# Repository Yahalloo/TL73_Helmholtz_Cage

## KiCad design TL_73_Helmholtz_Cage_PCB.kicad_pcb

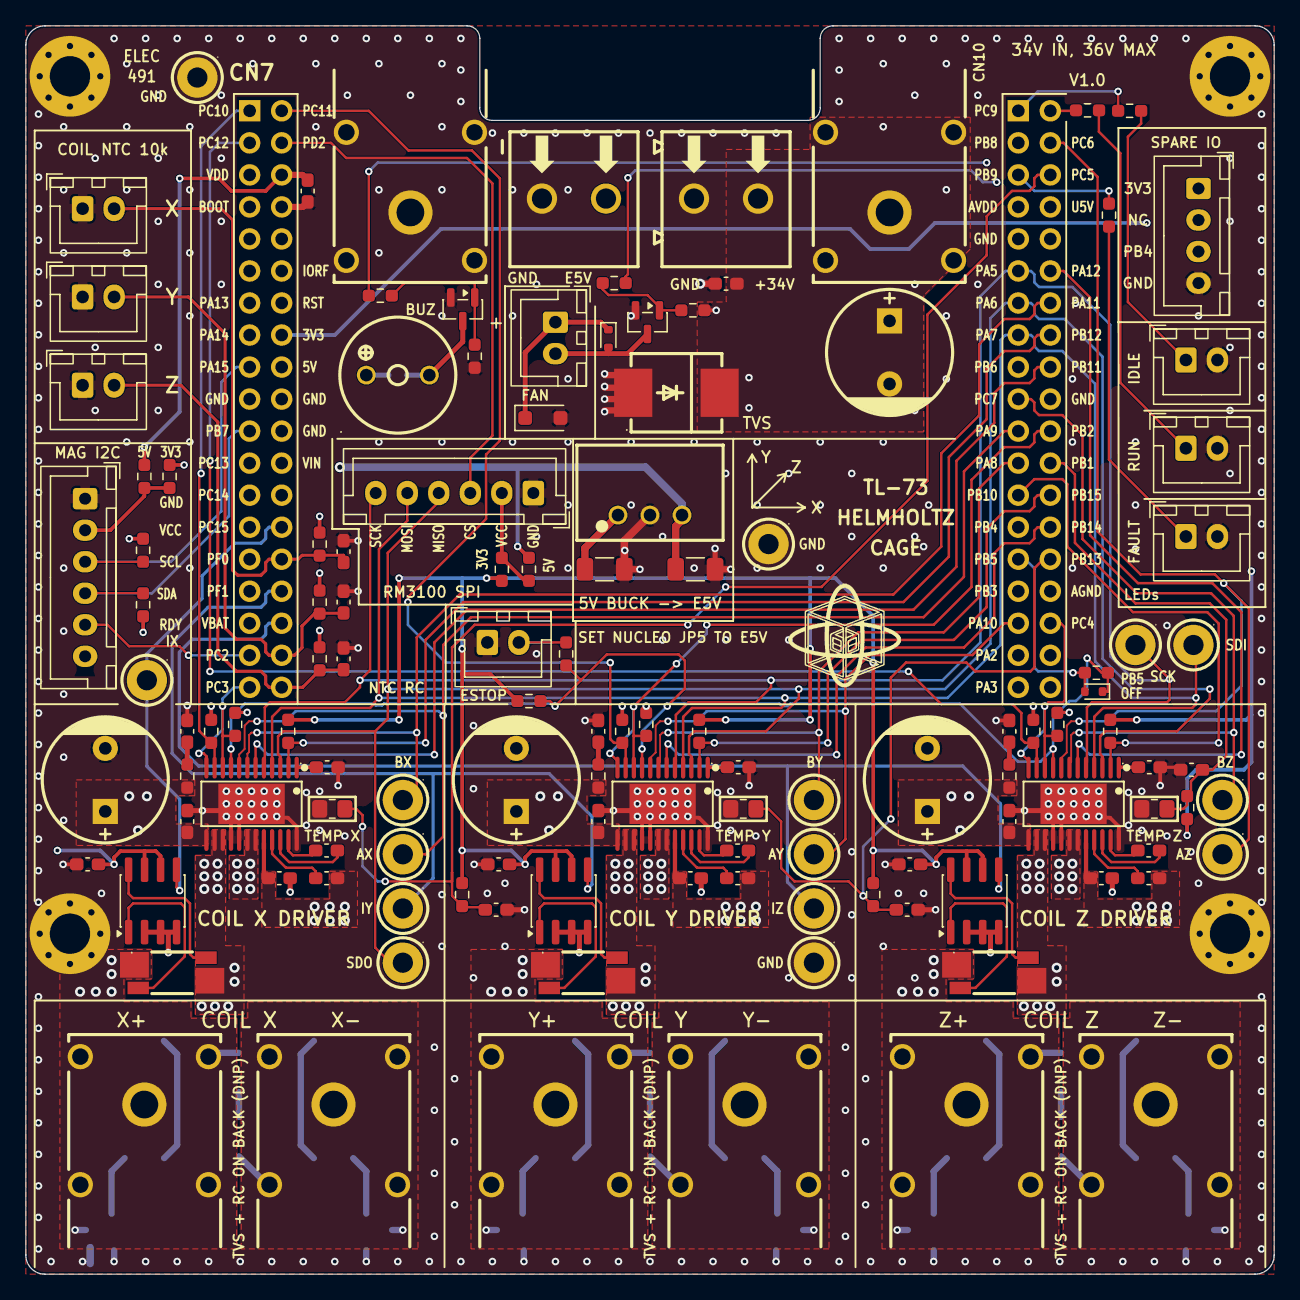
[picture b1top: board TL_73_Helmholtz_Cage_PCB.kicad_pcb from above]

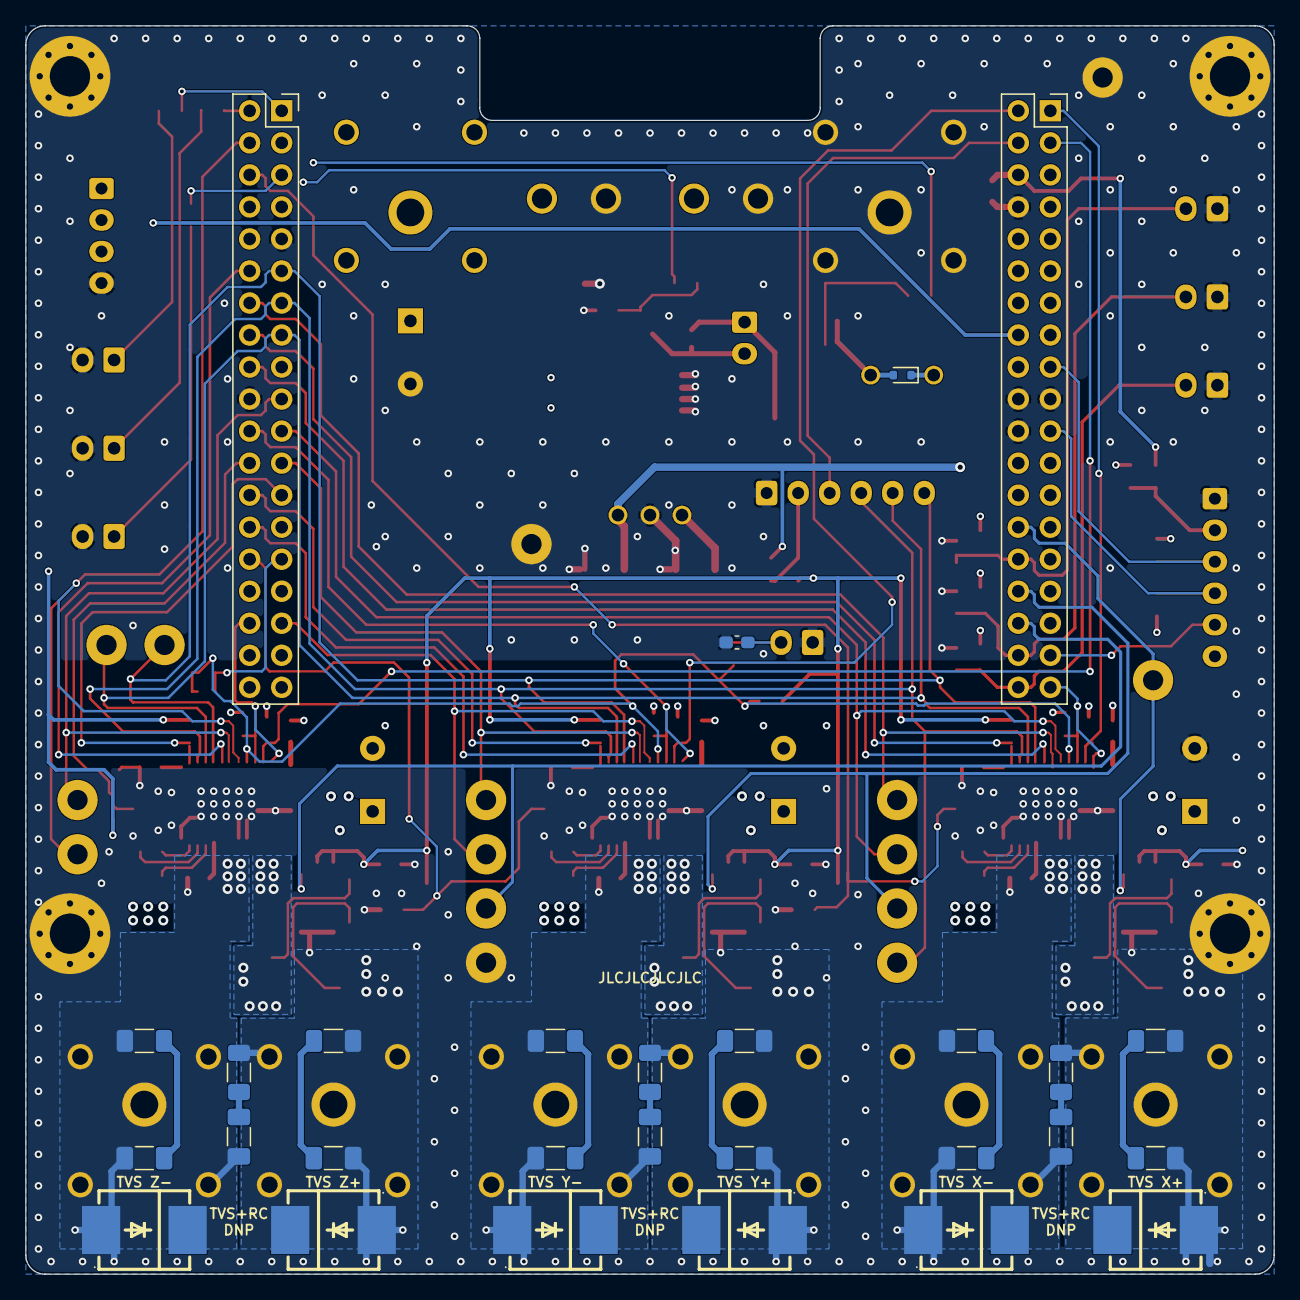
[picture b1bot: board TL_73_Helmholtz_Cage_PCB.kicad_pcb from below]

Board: 4 copper layers, 99.0 x 99.0 mm, 157 parts (28 on the bottom side), 95 nets.

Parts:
BZ201: TMB09A05; BUZ-TH_BD9.0-P5.00-D0.6-L-FD
C101: 10uF; C_1206_3216Metric_Pad1.33x1.80mm_HandSolder
C102: 22uF; C_1206_3216Metric_Pad1.33x1.80mm_HandSolder
C201, C202, C302, C305, C402, C405, C502, C505, C601, C701, C801, C901, C1001, C1101, C1202, C1401, C1402, C1403: 100nF; C_0603_1608Metric_Pad1.08x0.95mm_HandSolder
C301, C304, C401, C404, C501, C504: 1uF; C_0603_1608Metric_Pad1.08x0.95mm_HandSolder
C303, C403, C503: 47nF; C_0603_1608Metric_Pad1.08x0.95mm_HandSolder
C306, C406, C506: 10nF; C_0603_1608Metric_Pad1.08x0.95mm_HandSolder
C307, C407, C507: 330uF; CAP-TH_D10.0-P5.00_PA50V330M10X15_TL73
C1201: 470uF; CAP-TH_D10.0-P5.00_50ZLJ470M10X20_TL73
C1203, C1204, C1205, C1206, C1207, C1208, C1209, C1210, C1211: 470pF; C_1206_3216Metric_Pad1.33x1.80mm_HandSolder
CN1201, CN1203, CN1205, CN1207: 24.245.1; CONN-TH_24.245.1_RED_TL73
CN1202, CN1204, CN1206, CN1208: 24.245.2; CONN-TH_24.245.2_BLACK_TL73
D201: SMF5.0A; D_SOD-123F
D202, D203, D204: RB521S30T1G; D_SOD-523
D1201, D1202, D1203, D1204, D1205, D1206, D1207: SMDJ36A; SMC_L7.1-W6.2-LS8.1-RD
H101, H102, H103, H104: MountingHole_Pad; MountingHole_3.2mm_M3_Pad_Via
J201: CN7; PinSocket_2x19_P2.54mm_Vertical
J202: CN10; PinSocket_2x19_P2.54mm_Vertical
J203: LED_IDLE; JST_XH_B2B-XH-A_1x02_P2.50mm_Vertical
J204: STOP_SW_JST_XH; JST_XH_B2B-XH-A_1x02_P2.50mm_Vertical
J205: SPARE_IO_JST_XH; JST_XH_B4B-XH-A_1x04_P2.50mm_Vertical
J206: FAN_JST_XH; JST_XH_B2B-XH-A_1x02_P2.50mm_Vertical
J207: LED_RUN; JST_XH_B2B-XH-A_1x02_P2.50mm_Vertical
J208: LED_FAULT; JST_XH_B2B-XH-A_1x02_P2.50mm_Vertical
J901, J1001, J1101: NTC_JST_XH; JST_XH_B2B-XH-A_1x02_P2.50mm_Vertical
J1301: RM3100_JST_XH; JST_XH_B6B-XH-A_1x06_P2.50mm_Vertical
J1302: RM3100_SPI; JST_XH_B6B-XH-A_1x06_P2.50mm_Vertical
Q204, Q205: AO3400A; SOT-23
R104, R214, R215: 100k; R_0603_1608Metric_Pad0.98x0.95mm_HandSolder
R201, R202, R203: 150Ω; R_0603_1608Metric_Pad0.98x0.95mm_HandSolder
R204, R301, R302, R401, R402, R501, R502, R901, R1001, R1101, R1401, R1402, R1403: 10k; R_0603_1608Metric_Pad0.98x0.95mm_HandSolder
R205, R303, R403, R503: 330Ω; R_0603_1608Metric_Pad0.98x0.95mm_HandSolder
R209, R210: 100Ω; R_0603_1608Metric_Pad0.98x0.95mm_HandSolder
R304, R404, R504: 3.3Ω; R_0603_1608Metric_Pad0.98x0.95mm_HandSolder
R601, R701, R801: 10mΩ; RES-SMD_L6.4-W3.2_WSK2512R0100FEA
R1201, R1202, R1203, R1204, R1205, R1206, R1207, R1208, R1209: 33R; R_1206_3216Metric_Pad1.30x1.75mm_HandSolder
R1301, R1302: 2.2k; R_0603_1608Metric_Pad0.98x0.95mm_HandSolder
R1303, R1304, R1305, R1306: 0R; R_0603_1608Metric_Pad0.98x0.95mm_HandSolder
TH1401, TH1402, TH1403: 10k NTC; R_0805_2012Metric_Pad1.20x1.40mm_HandSolder
TP1, TP2, TP3, TP4, TP5, TP6, TP7, TP8, TP9, TP10, TP11, TP12, TP13, TP14, TP15: 5005; TESTPOINT-TH_BD3.2-D1.6_RED_TL73
U101: K7805-1000R3_C2992391; PWRM-TH_YLPTEC_K78XX-1000R3
U301, U401, U501: DRV8873SPWPR; HTSSOP-24_L7.8-W4.4-P0.65-LS6.4-TL-EP
U601, U701, U801: INA240A1DR; SOIC-8_3.9x4.9mm_P1.27mm
U1202: KF128-5.08-2P; CONN-TH_P5.08_KF128-5.08-2P
U1204: KF128-5.08-2P; CONN-TH_P5.08_KF128-5.08-2P_TL73_b

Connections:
+3V3: C601.1, C701.1, C801.1, J201.16, J205.1, R204.1, R301.1, R401.1, R501.1, R901.2, R1001.2, R1101.2, R1301.2, R1302.2, R1303.2, R1305.2, R1401.2, R1402.2, R1403.2, U601.6 (V+), U601.7 (REF1), U701.6 (V+), U701.7 (REF1), U801.6 (V+), U801.7 (REF1)
+34V: C101.1, C302.1, C304.1, C305.1, C307.1, C402.1, C404.1, C405.1, C407.1, C502.1, C504.1, C505.1, C507.1, C1201.1, C1202.1, CN1201.1, CN1201.2, D1201.1, R304.1, R404.1, R504.1, U101.1 (VIN), U301.13 (13VM), U301.20 (20VM), U401.13 (13VM), U401.20 (20VM), U501.13 (13VM), U501.20 (20VM), U1202.1
/BUZZER: J202.31, R210.1
/CurrentSense_CoilX/Icoil1: R601.4 (I1), U301.14 (14OUT2), U301.15 (15OUT2)
/CurrentSense_CoilX/Icoil2: CN1203.1, CN1203.2, D1202.1, R601.1 (I2), R1201.1, R1204.1
/CurrentSense_CoilX/SENSE_N: R601.2 (E2), U601.1 (-)
/CurrentSense_CoilX/SENSE_P: R601.3 (E1), U601.8 (+)
/CurrentSense_CoilY/Icoil1: R701.4 (I1), U401.14 (14OUT2), U401.15 (15OUT2)
/CurrentSense_CoilY/Icoil2: CN1205.1, CN1205.2, D1204.1, R701.1 (I2), R1202.1, R1206.1
/CurrentSense_CoilY/SENSE_N: R701.2 (E2), U701.1 (-)
/CurrentSense_CoilY/SENSE_P: R701.3 (E1), U701.8 (+)
/CurrentSense_CoilZ/Icoil1: R801.4 (I1), U501.14 (14OUT2), U501.15 (15OUT2)
/CurrentSense_CoilZ/Icoil2: CN1207.1, CN1207.2, D1206.1, R801.1 (I2), R1203.1, R1208.1
/CurrentSense_CoilZ/SENSE_N: R801.2 (E2), U801.1 (-)
/CurrentSense_CoilZ/SENSE_P: R801.3 (E1), U801.8 (+)
/DRV_DISABLE: D202.1, R104.1, R204.2, R205.1, U301.9 (9DISABLE), U401.9 (9DISABLE), U501.9 (9DISABLE)
/DRV_OFF: D202.2, J202.29, R104.2
/External_Connectors/CoilX-: C1203.2, CN1204.1, CN1204.2, D1203.1, R1205.2, U301.18 (18OUT1), U301.19 (19OUT1)
/External_Connectors/CoilY-: C1204.2, CN1206.1, CN1206.2, D1205.1, R1207.2, U401.18 (18OUT1), U401.19 (19OUT1)
/External_Connectors/CoilZ-: C1205.2, CN1208.1, CN1208.2, D1207.1, R1209.2, U501.18 (18OUT1), U501.19 (19OUT1)
/FAN_EN: J202.17, R209.1
/IPROPI_X: J201.37, R303.1, U301.10 (10IPROPL), U301.12 (12IPROPI2)
/IPROPI_Y: J202.22, R403.1, U401.10 (10IPROPL), U401.12 (12IPROPI2)
/IPROPI_Z: J202.34, R503.1, U501.10 (10IPROPL), U501.12 (12IPROPI2)
/ISENSE_CoilX: J201.28, TP1.1, U601.5
/ISENSE_CoilY: J201.32, TP2.1, U701.5
/ISENSE_CoilZ: J201.34, TP3.1, U801.5
/LED_FAULT: J202.5, R203.1
/LED_IDLE: J202.1, R201.1
/LED_RUN: J202.2, R202.1
/MAG_CS: J201.4, J1302.3
/MAG_DRDY: J201.35, J1301.5
/MAG_SCL: J201.17, J1301.3, R1301.1
/MAG_SDA: J201.21, J1301.4, R1302.1
/Magnetometer/MAG_VCC1: J1301.2, R1303.1, R1304.1
/Magnetometer/MAG_VCC2: J1302.2, R1305.1, R1306.1
/PWM_A_CoilX: J202.21, TP5.1, U301.8 (8PH/IN2)
/PWM_A_CoilY: J202.33, TP7.1, U401.8 (8PH/IN2)
/PWM_A_CoilZ: J202.4, TP9.1, U501.8 (8PH/IN2)
/PWM_B_CoilX: J202.14, TP6.1, U301.7 (7EN/IN1)
/PWM_B_CoilY: J202.23, TP8.1, U401.7 (7EN/IN1)
/PWM_B_CoilZ: J202.19, TP10.1, U501.7 (7EN/IN1)
/SPARE_PB4: J202.27, J205.3
/SPI_SCLK: J202.11, J1302.6, TP4.1, U301.5 (5SCLK), U401.5 (5SCLK), U501.5 (5SCLK)
/SPI_SDI: J202.15, J1302.5, TP12.1, U301.4 (4SDI), U401.4 (4SDI), U501.4 (4SDI)
/SPI_SDO: J202.13, J1302.4, TP11.1, U301.3 (3SDO), U401.3 (3SDO), U501.3 (3SDO)
/Temp_DrvX: C1401.1, J202.6, R1401.1, TH1401.1
/Temp_DrvY: C1402.1, J202.30, R1402.1, TH1402.1
/Temp_DrvZ: C1403.1, J202.24, R1403.1, TH1403.1
/Temp_SenseX: C901.1, J201.30, J901.2, R901.1
/Temp_SenseY: C1001.1, J201.36, J1001.2, R1001.1
/Temp_SenseZ: C1101.1, J201.38, J1101.2, R1101.1
/~FAULT_CoilX: J202.16, R301.2, U301.2 (2nFAULT)
/~FAULT_CoilY: J202.26, R401.2, U401.2 (2nFAULT)
/~FAULT_CoilZ: J202.25, R501.2, U501.2 (2nFAULT)
/~SCS_CoilX: J202.18, U301.6 (6nSCS)
/~SCS_CoilY: J202.28, U401.6 (6nSCS)
/~SCS_CoilZ: J202.12, U501.6 (6nSCS)
/~SLEEP_CoilX: J201.1, R302.1, U301.11 (11NSLEEP)
/~SLEEP_CoilY: J201.2, R402.1, U401.11 (11NSLEEP)
/~SLEEP_CoilZ: J201.3, R502.1, U501.11 (11NSLEEP)
E5V: BZ201.1, C102.1, C201.1, D201.1, D203.1, D204.1, J201.6, J206.1, R1304.2, R1306.2, U101.3 (+VO), U1204.1
GND: C101.2, C102.2, C201.2, C202.2, C301.2, C302.2, C305.2, C306.2, C307.2, C401.2, C402.2, C405.2, C406.2, C407.2, C501.2, C502.2, C505.2, C506.2, C507.2, C601.2, C701.2, C801.2, C901.2, C1001.2, C1101.2, C1201.2, C1202.2, C1206.2, C1207.1, C1208.2, C1209.1, C1210.2, C1211.1, C1401.2, C1402.2, C1403.2, CN1202.1, CN1202.2, D201.2, D1201.2, D1202.2, D1203.2, D1204.2, D1205.2, D1206.2, D1207.2, H101.1, H102.1, H103.1, H104.1, J201.8, J201.19, J201.20, J201.22, J202.9, J202.20, J203.2, J204.1, J205.4, J207.2, J208.2, J901.1, J1001.1, J1101.1, J1301.1, J1302.1, Q204.2, Q205.2, R214.2, R215.2, R302.2, R303.2, R402.2, R403.2, R502.2, R503.2, TH1401.2, TH1402.2, TH1403.2, TP13.1, TP14.1, TP15.1, U101.2 (GND), U301.16 (16SRC), U301.17 (17SRC), U301.24 (24GND), U301.25 (EP), U401.16 (16SRC), U401.17 (17SRC), U401.24 (24GND), U401.25 (EP), U501.16 (16SRC), U501.17 (17SRC), U501.24 (24GND), U501.25 (EP), U601.2 (GND), U601.3 (REF2), U601.4 (GND), U701.2 (GND), U701.3 (REF2), U701.4 (GND), U801.2 (GND), U801.3 (REF2), U801.4 (GND), U1202.2, U1204.2
unnamed: C306.1, R304.2
unnamed: C406.1, R404.2
unnamed: C506.1, R504.2
unnamed: C1203.1, R1201.2
unnamed: C1204.1, R1202.2
unnamed: C1205.1, R1203.2
unnamed: C1206.1, R1204.2
unnamed: C1207.2, R1205.1
unnamed: C1208.1, R1206.2
unnamed: C1209.2, R1207.1
unnamed: C1210.1, R1208.2
unnamed: C1211.2, R1209.1
unnamed: D203.2, J206.2, Q204.3
unnamed: BZ201.2, D204.2, Q205.3
unnamed: J203.1, R201.2
unnamed: C202.1, J204.2, R205.2
unnamed: J207.1, R202.2
unnamed: J208.1, R203.2
unnamed: Q204.1, R209.2, R214.1
unnamed: Q205.1, R210.2, R215.1
unnamed: C301.1, U301.1 (1DVDD)
unnamed: C304.2, U301.21 (21VCP)
unnamed: C303.2, U301.22 (22CPH)
unnamed: C303.1, U301.23 (23CPL)
unnamed: C401.1, U401.1 (1DVDD)
unnamed: C404.2, U401.21 (21VCP)
unnamed: C403.2, U401.22 (22CPH)
unnamed: C403.1, U401.23 (23CPL)
unnamed: C501.1, U501.1 (1DVDD)
unnamed: C504.2, U501.21 (21VCP)
unnamed: C503.2, U501.22 (22CPH)
unnamed: C503.1, U501.23 (23CPL)

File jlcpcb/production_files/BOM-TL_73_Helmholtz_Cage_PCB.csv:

Comment,Designator,Footprint,LCSC,Quantity
0R,"R1303,R1305",R_0603_1608Metric_Pad0.98x0.95mm_HandSolder,C21189,2
100k,"R104,R214,R215",R_0603_1608Metric_Pad0.98x0.95mm_HandSolder,C25803,3
100nF,"C1001,C1101,C1202,C1401,C1402,C1403,C201,C202,C302,C305,C402,C405,C502,C505,C601,C701,C801,C901",C_0603_1608Metric_Pad1.08x0.95mm_HandSolder,C24452,18
100Ω,"R209,R210",R_0603_1608Metric_Pad0.98x0.95mm_HandSolder,C22775,2
10k,"R1001,R1101,R1401,R1402,R1403,R204,R301,R302,R401,R402,R501,R502,R901",R_0603_1608Metric_Pad0.98x0.95mm_HandSolder,C95204,13
10k NTC,"TH1401,TH1402,TH1403",R_0805_2012Metric_Pad1.20x1.40mm_HandSolder,C511025,3
10mΩ,"R601,R701,R801",RES-SMD_L6.4-W3.2_WSK2512R0100FEA,C3985410,3
10nF,"C306,C406,C506",C_0603_1608Metric_Pad1.08x0.95mm_HandSolder,C1589,3
10uF,C101,C_1206_3216Metric_Pad1.33x1.80mm_HandSolder,C13585,1
150Ω,"R201,R202,R203",R_0603_1608Metric_Pad0.98x0.95mm_HandSolder,C22808,3
1uF,"C301,C304,C401,C404,C501,C504",C_0603_1608Metric_Pad1.08x0.95mm_HandSolder,C559769,6
2.2k,"R1301,R1302",R_0603_1608Metric_Pad0.98x0.95mm_HandSolder,C4190,2
22uF,C102,C_1206_3216Metric_Pad1.33x1.80mm_HandSolder,C12891,1
24.245.1,"CN1201,CN1203,CN1205,CN1207",CONN-TH_24.245.1_RED_TL73,C7437326,4
24.245.2,"CN1202,CN1204,CN1206,CN1208",CONN-TH_24.245.2_BLACK_TL73,C7437327,4
3.3Ω,"R304,R404,R504",R_0603_1608Metric_Pad0.98x0.95mm_HandSolder,C137725,3
330uF,"C307,C407,C507",CAP-TH_D10.0-P5.00_PA50V330M10X15_TL73,C46550457,3
330Ω,"R205,R303,R403,R503",R_0603_1608Metric_Pad0.98x0.95mm_HandSolder,C23138,4
470uF,C1201,CAP-TH_D10.0-P5.00_50ZLJ470M10X20_TL73,C2902875,1
47nF,"C303,C403,C503",C_0603_1608Metric_Pad1.08x0.95mm_HandSolder,C1622,3
5005,"TP1,TP10,TP11,TP12,TP13,TP14,TP15,TP2,TP3,TP4,TP5,TP6,TP7,TP8,TP9",TESTPOINT-TH_BD3.2-D1.6_RED_TL73,C2906763,15
AO3400A,"Q204,Q205",SOT-23,C20917,2
CN10,J202,PinSocket_2x19_P2.54mm_Vertical,C22373924,1
CN7,J201,PinSocket_2x19_P2.54mm_Vertical,C22373924,1
DRV8873SPWPR,"U301,U401,U501",HTSSOP-24_L7.8-W4.4-P0.65-LS6.4-TL-EP,C2150662,3
FAN_JST_XH,J206,JST_XH_B2B-XH-A_1x02_P2.50mm_Vertical,C158012,1
INA240A1DR,"U601,U701,U801",SOIC-8_3.9x4.9mm_P1.27mm,C2060769,3
K7805-1000R3_C2992391,U101,PWRM-TH_YLPTEC_K78XX-1000R3,C2992391,1
KF128-5.08-2P,"U1202,U1204",CONN-TH_P5.08_KF128-5.08-2P,C474952,2
LED_FAULT,J208,JST_XH_B2B-XH-A_1x02_P2.50mm_Vertical,C158012,1
LED_IDLE,J203,JST_XH_B2B-XH-A_1x02_P2.50mm_Vertical,C158012,1
LED_RUN,J207,JST_XH_B2B-XH-A_1x02_P2.50mm_Vertical,C158012,1
NTC_JST_XH,"J1001,J1101,J901",JST_XH_B2B-XH-A_1x02_P2.50mm_Vertical,C158012,3
RB521S30T1G,"D202,D203,D204",D_SOD-523,C145179,3
RM3100_JST_XH,J1301,JST_XH_B6B-XH-A_1x06_P2.50mm_Vertical,C144397,1
RM3100_SPI,J1302,JST_XH_B6B-XH-A_1x06_P2.50mm_Vertical,C144397,1
SMDJ36A,D1201,SMC_L7.1-W6.2-LS8.1-RD,C108363,1
SMF5.0A,D201,D_SOD-123F,C151296,1
SPARE_IO_JST_XH,J205,JST_XH_B4B-XH-A_1x04_P2.50mm_Vertical,C144395,1
STOP_SW_JST_XH,J204,JST_XH_B2B-XH-A_1x02_P2.50mm_Vertical,C158012,1
TMB09A05,BZ201,BUZ-TH_BD9.0-P5.00-D0.6-L-FD,C49246939,1
MountingHole_Pad,H104,MountingHole_3.2mm_M3_Pad_Via,,1
MountingHole_Pad,H103,MountingHole_3.2mm_M3_Pad_Via,,1
MountingHole_Pad,H101,MountingHole_3.2mm_M3_Pad_Via,,1
MountingHole_Pad,H102,MountingHole_3.2mm_M3_Pad_Via,,1

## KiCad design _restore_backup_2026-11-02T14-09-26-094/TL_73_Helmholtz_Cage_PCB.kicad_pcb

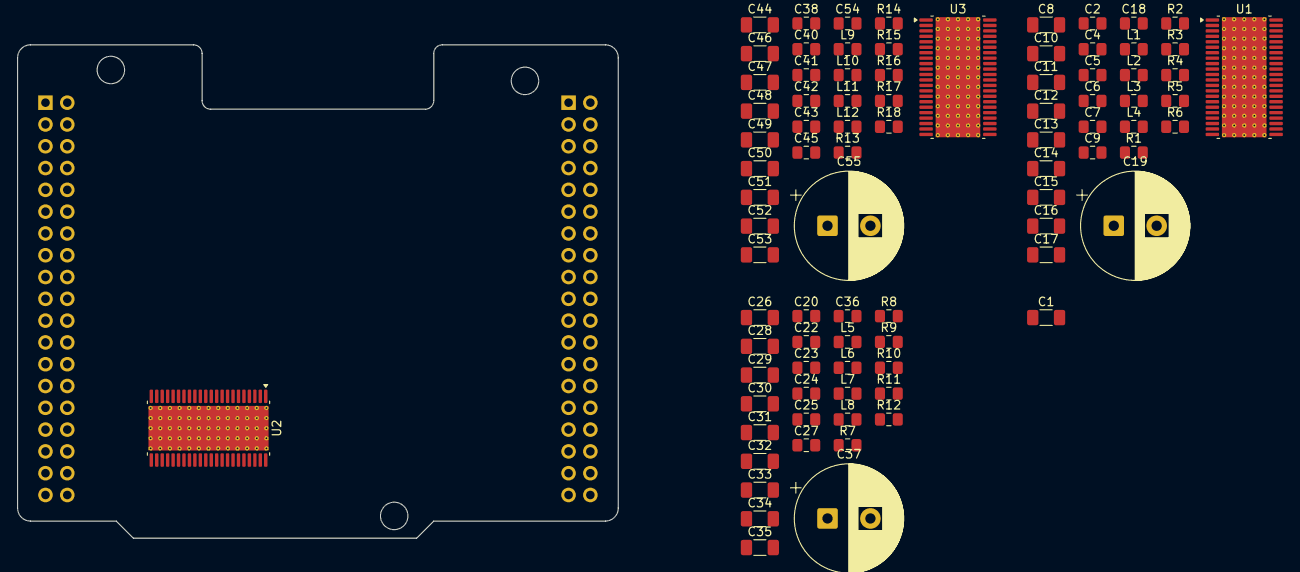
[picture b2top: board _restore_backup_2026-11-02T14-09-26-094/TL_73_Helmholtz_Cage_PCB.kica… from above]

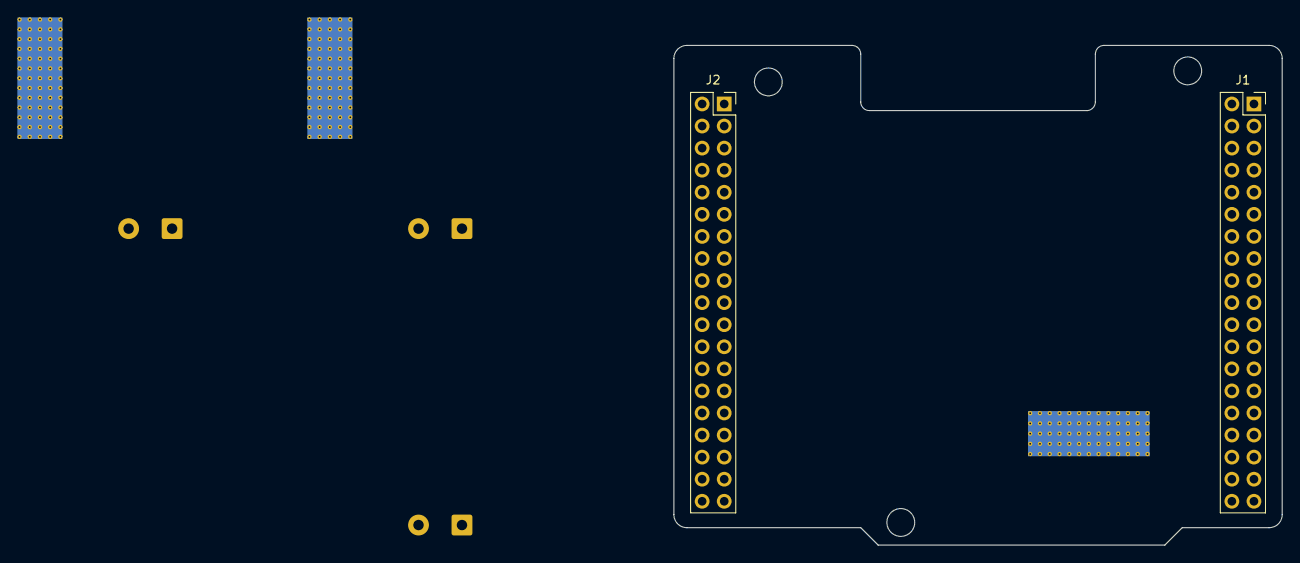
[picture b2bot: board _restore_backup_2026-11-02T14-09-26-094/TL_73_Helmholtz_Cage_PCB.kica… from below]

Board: 2 copper layers, 70.0 x 57.5 mm, 90 parts (2 on the bottom side), 64 nets, no tracks yet.

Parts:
C1, C8, C10, C11, C12, C13, C14, C15, C16, C17, C26, C28, C29, C30, C31, C32, C33, C34, C35, C44, C46, C47, C48, C49, C50, C51, C52, C53: 100nF; C_1206_3216Metric_Pad1.33x1.80mm_HandSolder
C2, C5, C6, C7, C9, C20, C23, C24, C25, C27, C38, C41, C42, C43, C45: 1uF; C_0805_2012Metric_Pad1.18x1.45mm_HandSolder
C4, C22, C40: 47uF; C_0805_2012Metric_Pad1.18x1.45mm_HandSolder
C18, C36, C54: 10 nF; C_0805_2012Metric_Pad1.18x1.45mm_HandSolder
C19, C37, C55: 1000uF; CP_Radial_D12.5mm_P5.00mm
H1, H2, H3: MountingHole; MountingHole_3.2mm_M3
J1: CN7; PinSocket_2x19_P2.54mm_Vertical
J2: CN10; PinSocket_2x19_P2.54mm_Vertical
L1, L2, L3, L4, L5, L6, L7, L8, L9, L10, L11, L12: 30Ω@100MHz; C_0805_2012Metric_Pad1.18x1.45mm_HandSolder
R1, R2, R3, R7, R8, R9, R13, R14, R15: 10k; C_0805_2012Metric_Pad1.18x1.45mm_HandSolder
R4, R10, R16: 1; C_0805_2012Metric_Pad1.18x1.45mm_HandSolder
R5, R11, R17: 36k; C_0805_2012Metric_Pad1.18x1.45mm_HandSolder
R6, R12, R18: 3.3; C_0805_2012Metric_Pad1.18x1.45mm_HandSolder
U1, U2, U3: DRV8412; HTSSOP-44-1EP_6.1x14mm_P0.635mm_EP5.2x14mm_Mask4.31x8.26mm_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

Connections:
+3V3: J1.16, R1.1, R3.1, R7.1, R9.1, R13.1, R15.1
+12V: C1.1, J1.24
+24V: C10.2, C11.2, C12.2, C17.2, C19.1, C28.2, C29.2, C30.2, C35.2, C37.1, C46.2, C47.2, C48.2, C53.2, C55.1, R6.1, R12.1, R18.1, U1.26 (PVDD_A), U1.27 (PVDD_A), U1.32 (PVDD_B), U1.35 (PVDD_C), U1.40 (PVDD_D), U1.41 (PVDD_D), U2.26 (PVDD_A), U2.27 (PVDD_A), U2.32 (PVDD_B), U2.35 (PVDD_C), U2.40 (PVDD_D), U2.41 (PVDD_D), U3.26 (PVDD_A), U3.27 (PVDD_A), U3.32 (PVDD_B), U3.35 (PVDD_C), U3.40 (PVDD_D), U3.41 (PVDD_D)
/Current_Driver_Distribution/VOUTA_CoilX: L1.2, L2.2
/Current_Driver_Distribution/VOUTA_CoilY: L5.2, L6.2
/Current_Driver_Distribution/VOUTA_CoilZ: L9.2, L10.2
/Current_Driver_Distribution/VOUTB_CoilX: L3.2, L4.2
/Current_Driver_Distribution/VOUTB_CoilY: L7.2, L8.2
/Current_Driver_Distribution/VOUTB_CoilZ: L11.2, L12.2
/PWM_A_CoilX: J2.23, U1.17 (PWM_A)
/PWM_A_CoilY: J2.33, U2.17 (PWM_A)
/PWM_A_CoilZ: J2.4, U3.17 (PWM_A)
/PWM_B_CoilX: J2.21, U1.15 (PWM_B)
/PWM_B_CoilY: J2.14, U2.15 (PWM_B)
/PWM_B_CoilZ: J2.19, U3.15 (PWM_B)
/~FAULT_CoilX: J2.16, R3.2, U1.18 (~FAULT)
/~FAULT_CoilY: J2.26, R9.2, U2.18 (~FAULT)
/~FAULT_CoilZ: J2.22, R15.2, U3.18 (~FAULT)
/~OTW_CoilX: J2.18, R1.2, U1.21 (~OTW)
/~OTW_CoilY: J2.28, R7.2, U2.21 (~OTW)
/~OTW_CoilZ: J2.24, R13.2, U3.21 (~OTW)
/~RESET_CoilX: J1.1, R2.1, U1.6 (~RESET_CD), U1.16 (~RESET_AB)
/~RESET_CoilY: J1.2, R8.1, U2.6 (~RESET_CD), U2.16 (~RESET_AB)
/~RESET_CoilZ: J1.3, R14.1, U3.6 (~RESET_CD), U3.16 (~RESET_AB)
GND: C1.2, C2.1, C4.2, C5.1, C6.1, C7.2, C9.1, C10.1, C11.1, C12.1, C17.1, C18.2, C19.2, C20.1, C22.2, C23.1, C24.1, C25.2, C27.1, C28.1, C29.1, C30.1, C35.1, C36.2, C37.2, C38.1, C40.2, C41.1, C42.1, C43.2, C45.1, C46.1, C47.1, C48.1, C53.1, C54.2, C55.2, J1.8, J1.19, J1.20, J1.22, J2.20, R2.2, R4.2, R8.2, R10.2, R14.2, R16.2, U1.3 (NC/GND), U1.4 (NC/GND), U1.5 (PWM_D), U1.7 (PWM_C), U1.13 (GND), U1.19 (NC/GND), U1.20 (NC/GND), U1.25 (NC/GND), U1.29 (GND_A), U1.30 (GND_B), U1.37 (GND_C), U1.38 (GND_D), U1.42 (NC/GND), U1.45 (EP), U2.3 (NC/GND), U2.4 (NC/GND), U2.5 (PWM_D), U2.7 (PWM_C), U2.13 (GND), U2.19 (NC/GND), U2.20 (NC/GND), U2.25 (NC/GND), U2.29 (GND_A), U2.30 (GND_B), U2.37 (GND_C), U2.38 (GND_D), U2.42 (NC/GND), U2.45 (EP), U3.3 (NC/GND), U3.4 (NC/GND), U3.5 (PWM_D), U3.7 (PWM_C), U3.13 (GND), U3.19 (NC/GND), U3.20 (NC/GND), U3.25 (NC/GND), U3.29 (GND_A), U3.30 (GND_B), U3.37 (GND_C), U3.38 (GND_D), U3.42 (NC/GND), U3.45 (EP)
unnamed: C18.1, R6.2
unnamed: C36.1, R12.2
unnamed: C54.1, R18.2
unnamed: C2.2, C4.1, C5.2, C6.2, C7.1, C9.2, U1.1 (GVDD_C), U1.2 (VDD), U1.22 (GVDD_B), U1.23 (GVDD_A), U1.44 (GVDD_D)
unnamed: C20.2, C22.1, C23.2, C24.2, C25.1, C27.2, U2.1 (GVDD_C), U2.2 (VDD), U2.22 (GVDD_B), U2.23 (GVDD_A), U2.44 (GVDD_D)
unnamed: C38.2, C40.1, C41.2, C42.2, C43.1, C45.2, U3.1 (GVDD_C), U3.2 (VDD), U3.22 (GVDD_B), U3.23 (GVDD_A), U3.44 (GVDD_D)
unnamed: C8.1, R4.1, R5.1, U1.8 (M1), U1.10 (M3), U1.12 (AGND)
unnamed: C13.1, U1.24 (BST_A)
unnamed: C14.1, U1.33 (BST_B)
unnamed: C15.1, U1.34 (BST_C)
unnamed: C16.1, U1.43 (BST_D)
unnamed: C8.2, U1.9 (M2), U1.11 (VREG)
unnamed: R5.2, U1.14 (OC_ADJ)
unnamed: C13.2, L1.1, U1.28 (OUT_A)
unnamed: C14.2, L2.1, U1.31 (OUT_B)
unnamed: C15.2, L3.1, U1.36 (OUT_C)
unnamed: C16.2, L4.1, U1.39 (OUT_D)
unnamed: C26.1, R10.1, R11.1, U2.8 (M1), U2.10 (M3), U2.12 (AGND)
unnamed: C31.1, U2.24 (BST_A)
unnamed: C32.1, U2.33 (BST_B)
unnamed: C33.1, U2.34 (BST_C)
unnamed: C34.1, U2.43 (BST_D)
unnamed: C26.2, U2.9 (M2), U2.11 (VREG)
unnamed: R11.2, U2.14 (OC_ADJ)
unnamed: C31.2, L5.1, U2.28 (OUT_A)
unnamed: C32.2, L6.1, U2.31 (OUT_B)
unnamed: C33.2, L7.1, U2.36 (OUT_C)
unnamed: C34.2, L8.1, U2.39 (OUT_D)
unnamed: C44.1, R16.1, R17.1, U3.8 (M1), U3.10 (M3), U3.12 (AGND)
unnamed: C49.1, U3.24 (BST_A)
unnamed: C50.1, U3.33 (BST_B)
unnamed: C51.1, U3.34 (BST_C)
unnamed: C52.1, U3.43 (BST_D)
unnamed: C44.2, U3.9 (M2), U3.11 (VREG)
unnamed: R17.2, U3.14 (OC_ADJ)
unnamed: C49.2, L9.1, U3.28 (OUT_A)
unnamed: C50.2, L10.1, U3.31 (OUT_B)
unnamed: C51.2, L11.1, U3.36 (OUT_C)
unnamed: C52.2, L12.1, U3.39 (OUT_D)
